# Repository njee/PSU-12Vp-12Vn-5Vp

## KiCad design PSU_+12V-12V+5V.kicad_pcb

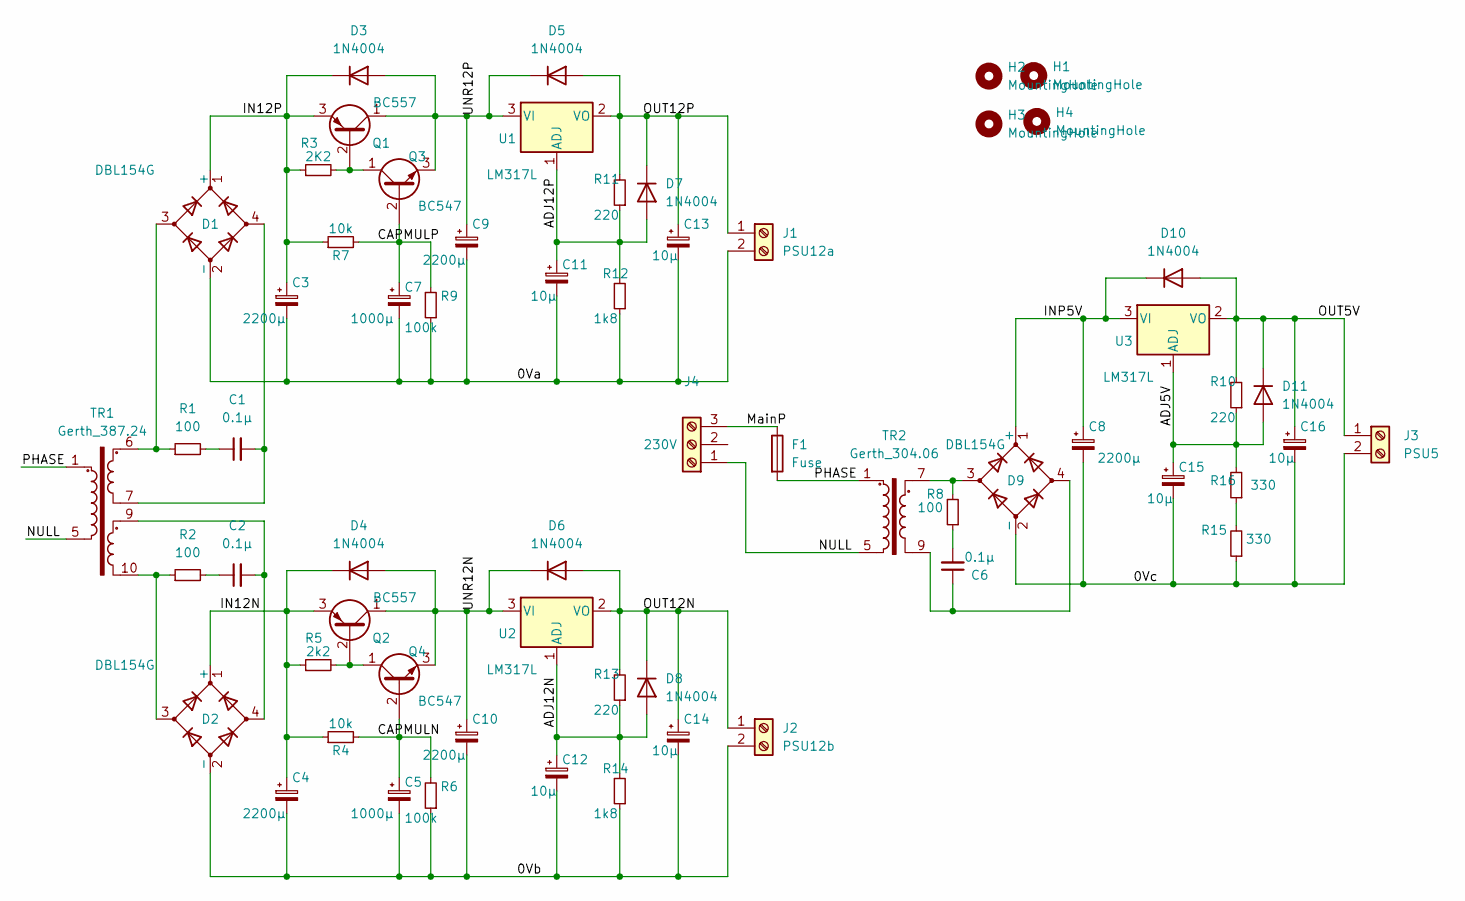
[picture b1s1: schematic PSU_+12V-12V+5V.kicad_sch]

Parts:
C1, C2, C6: 0.1µ; C_Disc_D6.0mm_W2.5mm_P5.00mm
C3, C4, C8, C9, C10: 2200µ; CP_Radial_D16.0mm_P7.50mm
C5, C7: 1000µ; CP_Radial_D10.0mm_P5.00mm
C11, C12, C13, C14, C15, C16: 10µ; CP_Radial_D5.0mm_P2.50mm
D1, D2, D9: DBL154G; DBL_4
D3, D4, D5, D6, D7, D8, D10, D11: 1N4004; D_DO-41_SOD81_P10.16mm_Horizontal
F1: Fuse; Fuse_Littelfuse-PTF15
H1, H2, H3, H4: MountingHole; MountingHole_3.2mm_M3
J1: PSU12a; TerminalBlock_Phoenix_MKDS-1,5-2_1x02_P5.00mm_Horizontal
J2: PSU12b; TerminalBlock_Phoenix_MKDS-1,5-2_1x02_P5.00mm_Horizontal
J3: PSU5; TerminalBlock_Phoenix_MKDS-1,5-2_1x02_P5.00mm_Horizontal
J4: 230V; TerminalBlock_Phoenix_MKDS-1,5-3_1x03_P5.00mm_Horizontal
Q1, Q2: BC557; TO-92_Inline_Wide
Q3, Q4: BC547; TO-92_Inline_Wide
R1, R2, R8: 100; R_1206_3216Metric_Pad1.30x1.75mm_HandSolder
R3: 2K2; R_1206_3216Metric_Pad1.30x1.75mm_HandSolder
R4, R7: 10k; R_1206_3216Metric_Pad1.30x1.75mm_HandSolder
R5: 2k2; R_1206_3216Metric_Pad1.30x1.75mm_HandSolder
R6, R9: 100k; R_1206_3216Metric_Pad1.30x1.75mm_HandSolder
R10, R11, R13: 220; R_1206_3216Metric_Pad1.30x1.75mm_HandSolder
R12, R14: 1k8; R_1206_3216Metric_Pad1.30x1.75mm_HandSolder
R15, R16: 330; R_1206_3216Metric_Pad1.30x1.75mm_HandSolder
TR1: Gerth_387.24; 387.24_3.6VA
TR2: Gerth_304.06; 304.06_1.8VA
U1, U2, U3: LM317L; LM317L_TO92

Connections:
/0Va: C3.2, C7.2, C9.2, C11.2, C13.2, D1.2 (-), J1.2, R9.1, R12.1
/0Vb: C4.2, C5.2, C10.2, C12.2, C14.2, D2.2 (-), J2.2, R6.1, R14.1
/0Vc: C8.2, C15.2, C16.2, D9.2 (-), J3.2, R15.1
/ADJ5V: C15.1, D11.2 (A), R10.1, R16.2, U3.1 (ADJ)
/ADJ12N: C12.1, D8.2 (A), R13.1, R14.2, U2.1 (ADJ)
/ADJ12P: C11.1, D7.2 (A), R11.1, R12.2, U1.1 (ADJ)
/CAPMULN: C5.1, Q4.2 (B), R4.2, R6.2
/CAPMULP: C7.1, Q3.2 (B), R7.2, R9.2
/IN12N: C4.1, D2.1 (+), D4.1 (K), Q2.3 (E), R4.1, R5.1
/IN12P: C3.1, D1.1 (+), D3.1 (K), Q1.3 (E), R3.1, R7.1
/INP5V: C8.1, D9.1 (+), D10.1 (K), U3.3 (VI)
/MainP: F1.1, J4.3
/NULL: J4.1, TR1.5, TR2.5
/OUT5V: C16.1, D10.2 (A), D11.1 (K), J3.1, R10.2, U3.2 (VO)
/OUT12N: C14.1, D6.2 (A), D8.1 (K), J2.1, R13.2, U2.2 (VO)
/OUT12P: C13.1, D5.2 (A), D7.1 (K), J1.1, R11.2, U1.2 (VO)
/PHASE: F1.2, TR1.1, TR2.1
/UNR12N: C10.1, D4.2 (A), D6.1 (K), Q2.1 (C), Q4.3 (E), U2.3 (VI)
/UNR12P: C9.1, D3.2 (A), D5.1 (K), Q1.1 (C), Q3.3 (E), U1.3 (VI)
unnamed: C1.1, R1.2
unnamed: C1.2, D1.4, TR1.7
unnamed: C2.1, R2.2
unnamed: C2.2, D2.4, TR1.9
unnamed: C6.1, D9.4, TR2.9
unnamed: C6.2, R8.1
unnamed: D1.3, R1.1, TR1.6
unnamed: D2.3, R2.1, TR1.10
unnamed: D9.3, R8.2, TR2.7
unnamed: Q1.2 (B), Q3.1 (C), R3.2
unnamed: Q2.2 (B), Q4.1 (C), R5.2
unnamed: R15.2, R16.1

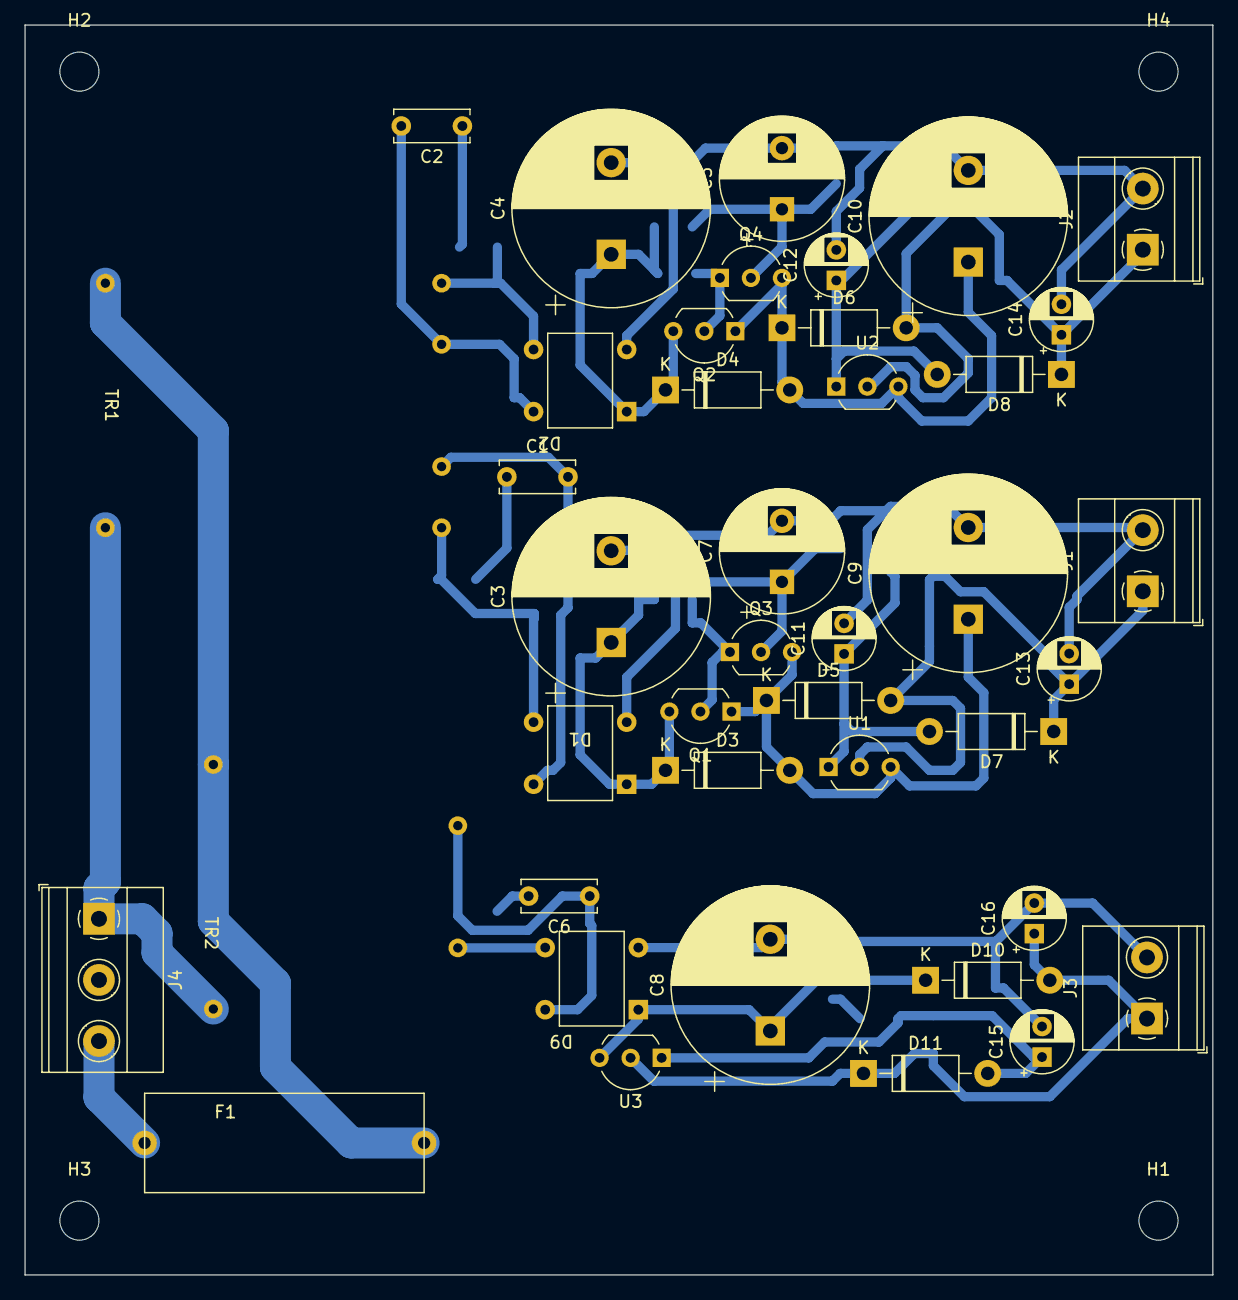
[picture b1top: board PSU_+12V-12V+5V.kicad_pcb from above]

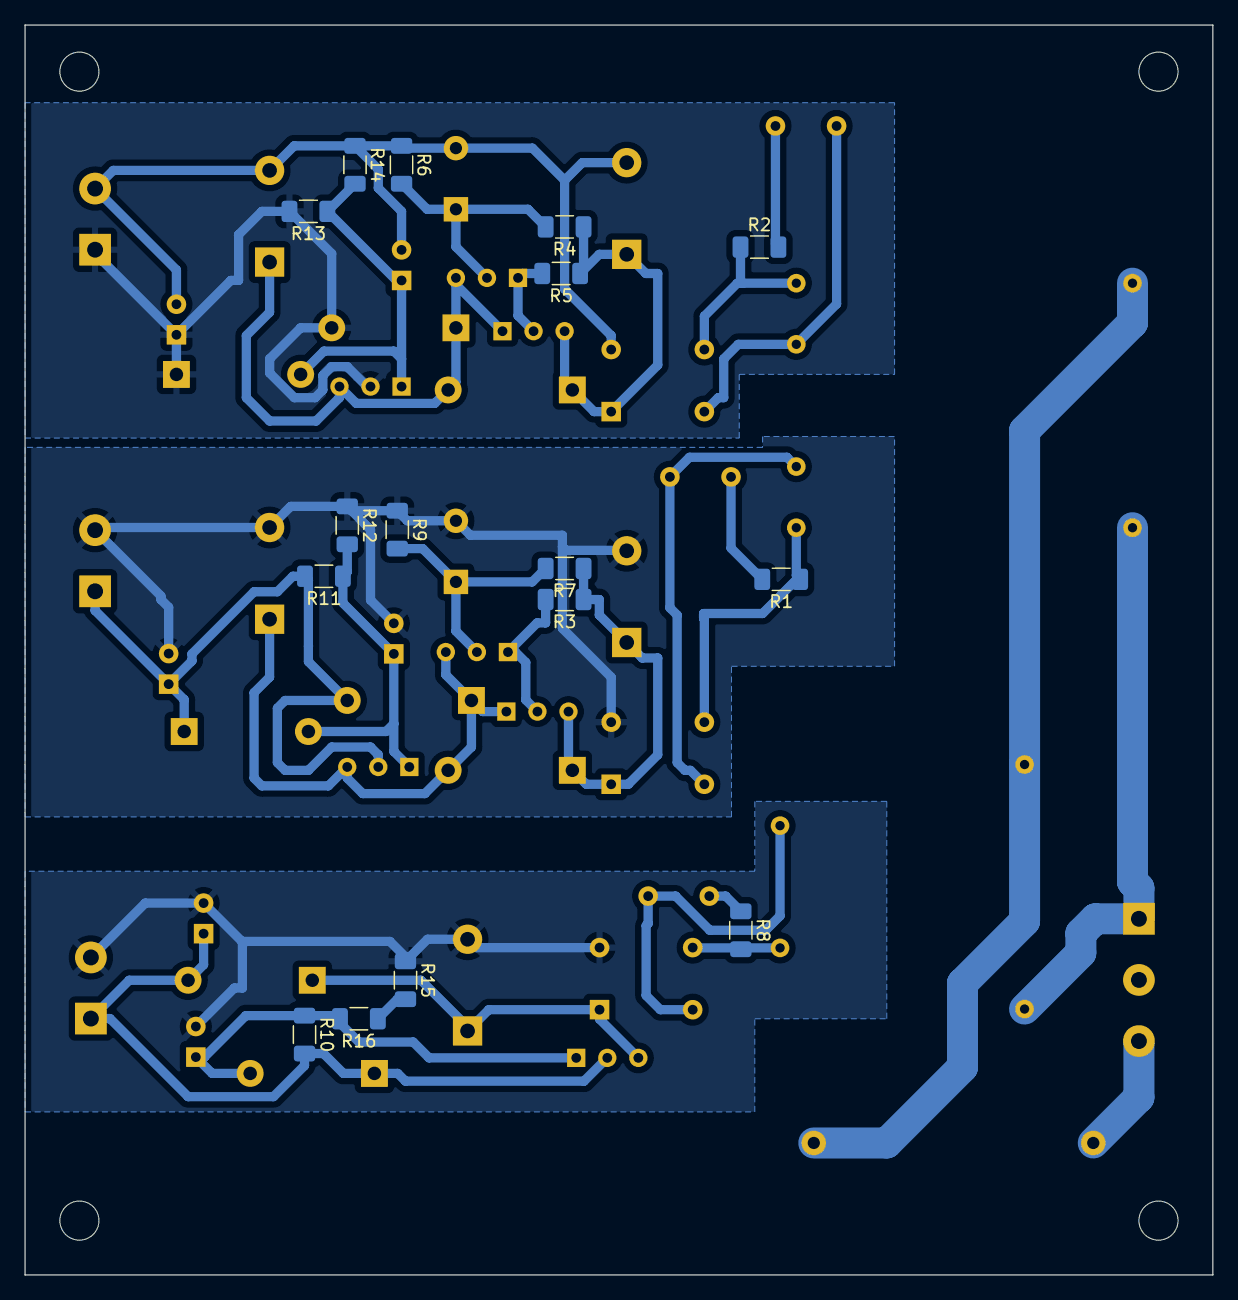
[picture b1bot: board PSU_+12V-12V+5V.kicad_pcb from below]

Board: 2 copper layers, 97.2 x 102.2 mm, 61 parts (16 on the bottom side), 31 nets.

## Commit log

2022-11-23 Herschikkingen om filled area te optimaizeren
2022-11-23 Some shifting
2022-11-23 Add 5V part + 230 volt connection
2022-11-27 Changed footprint of LM317L
2022-11-28 Aanpassing ijkweerstand 5V
2022-11-28 Changed type capacitor
2022-12-05 Put some nets
2022-12-11 Changed some values
2022-12-12 Change page setup for printing on A4
